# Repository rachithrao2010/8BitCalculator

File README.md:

Hey everyone!
This is my 8 bit calculator. it uses 8 1 bit full adders chained together. each 1 bit full adder module contains 9 NOR gates, with 2 2N3904 transistors, 2 10K resistors, and 1 1K resistor.
Heres a 3D render:

And here's a screensot of the routed board:

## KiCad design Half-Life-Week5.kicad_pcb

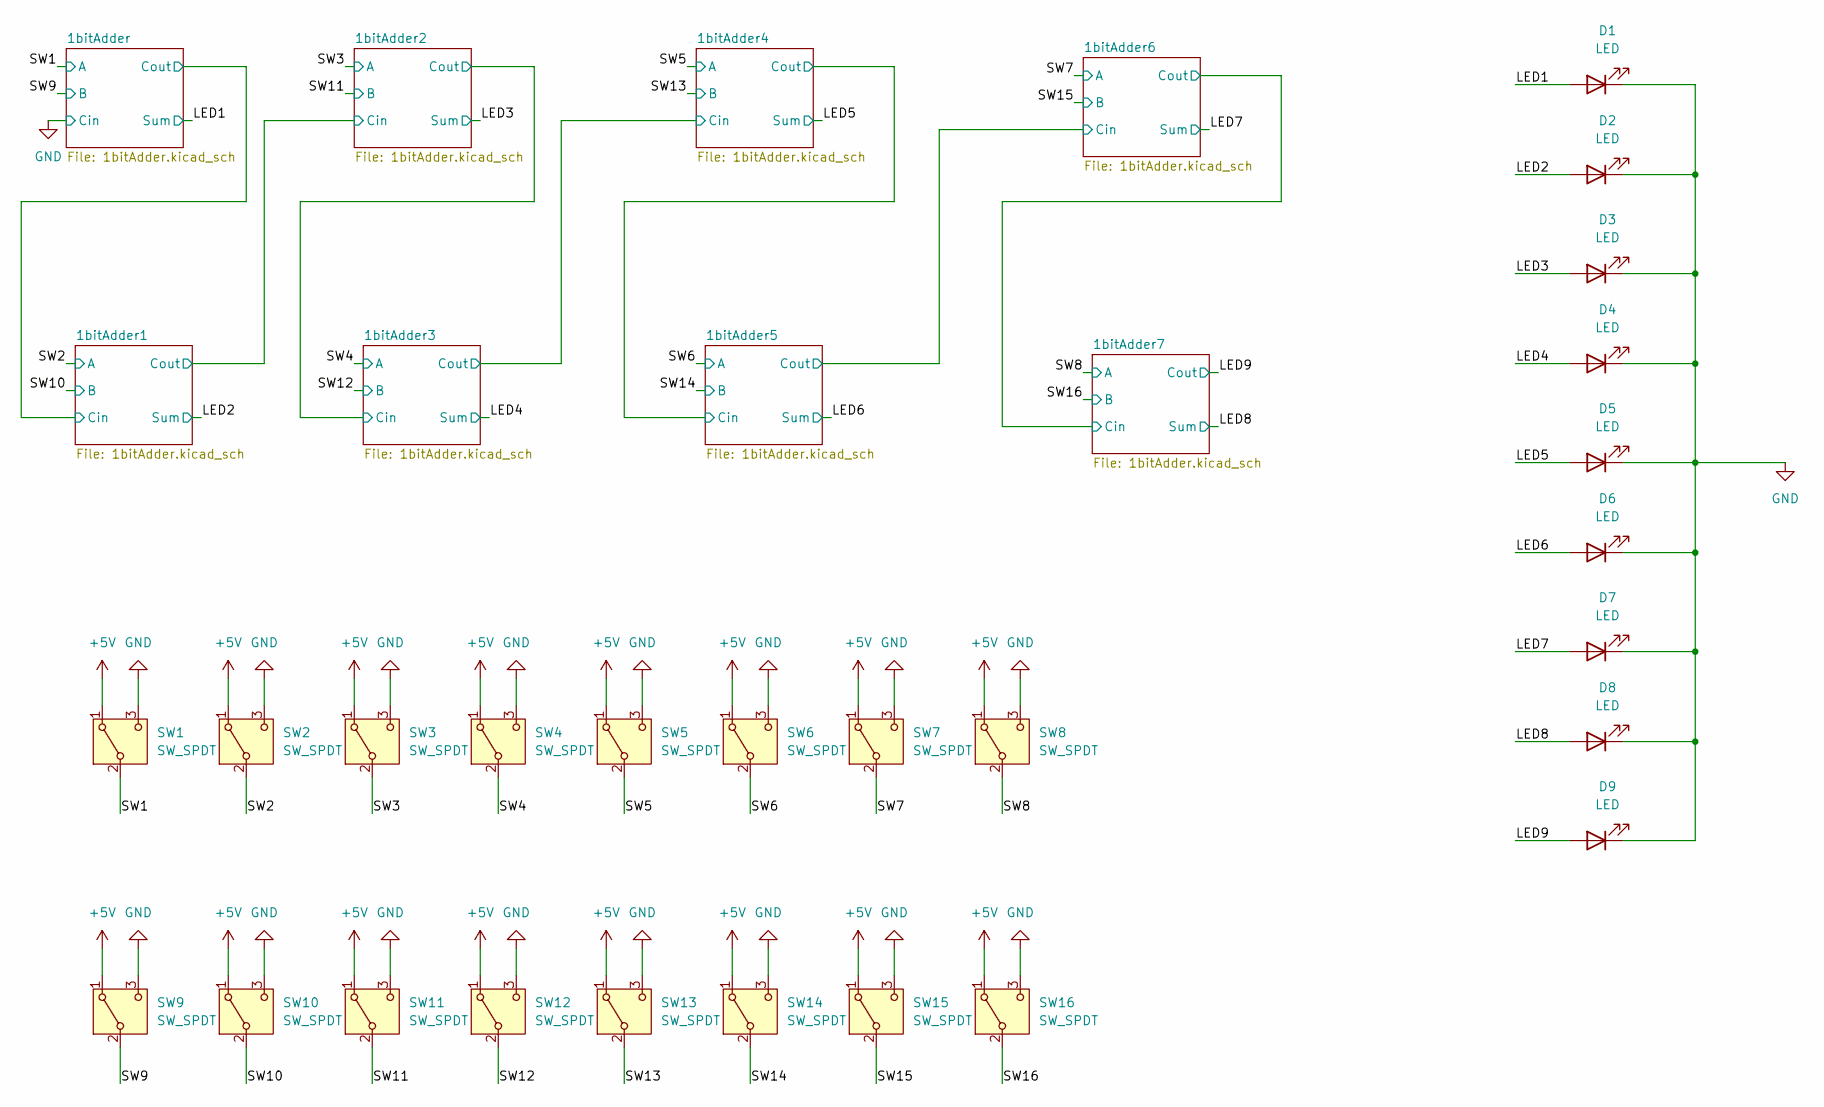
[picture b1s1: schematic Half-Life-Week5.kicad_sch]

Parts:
D1, D2, D3, D4, D5, D6, D7, D8, D9: LED; LED_D3.0mm
SW1, SW2, SW3, SW4, SW5, SW6, SW7, SW8, SW9, SW10, SW11, SW12, SW13, SW14, SW15, SW16: SW_SPDT; SW_Slide_SPDT_Straight_CK_OS102011MS2Q

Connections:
+5V: SW1.1 (A), SW2.1 (A), SW3.1 (A), SW4.1 (A), SW5.1 (A), SW6.1 (A), SW7.1 (A), SW8.1 (A), SW9.1 (A), SW10.1 (A), SW11.1 (A), SW12.1 (A), SW13.1 (A), SW14.1 (A), SW15.1 (A), SW16.1 (A); also elsewhere on the board
/LED1: D1.2 (A); also elsewhere on the board
/LED2: D2.2 (A); also elsewhere on the board
/LED3: D3.2 (A); also elsewhere on the board
/LED4: D4.2 (A); also elsewhere on the board
/LED5: D5.2 (A); also elsewhere on the board
/LED6: D6.2 (A); also elsewhere on the board
/LED7: D7.2 (A); also elsewhere on the board
/LED8: D8.2 (A); also elsewhere on the board
/LED9: D9.2 (A); also elsewhere on the board
/SW1: SW1.2 (B); also elsewhere on the board
/SW2: SW2.2 (B); also elsewhere on the board
/SW3: SW3.2 (B); also elsewhere on the board
/SW4: SW4.2 (B); also elsewhere on the board
/SW5: SW5.2 (B); also elsewhere on the board
/SW6: SW6.2 (B); also elsewhere on the board
/SW7: SW7.2 (B); also elsewhere on the board
/SW8: SW8.2 (B); also elsewhere on the board
/SW9: SW9.2 (B); also elsewhere on the board
/SW10: SW10.2 (B); also elsewhere on the board
/SW11: SW11.2 (B); also elsewhere on the board
/SW12: SW12.2 (B); also elsewhere on the board
/SW13: SW13.2 (B); also elsewhere on the board
/SW14: SW14.2 (B); also elsewhere on the board
/SW15: SW15.2 (B); also elsewhere on the board
/SW16: SW16.2 (B); also elsewhere on the board
GND: D1.1 (K), D2.1 (K), D3.1 (K), D4.1 (K), D5.1 (K), D6.1 (K), D7.1 (K), D8.1 (K), D9.1 (K), SW1.3 (C), SW2.3 (C), SW3.3 (C), SW4.3 (C), SW5.3 (C), SW6.3 (C), SW7.3 (C), SW8.3 (C), SW9.3 (C), SW10.3 (C), SW11.3 (C), SW12.3 (C), SW13.3 (C), SW14.3 (C), SW15.3 (C), SW16.3 (C); also elsewhere on the board

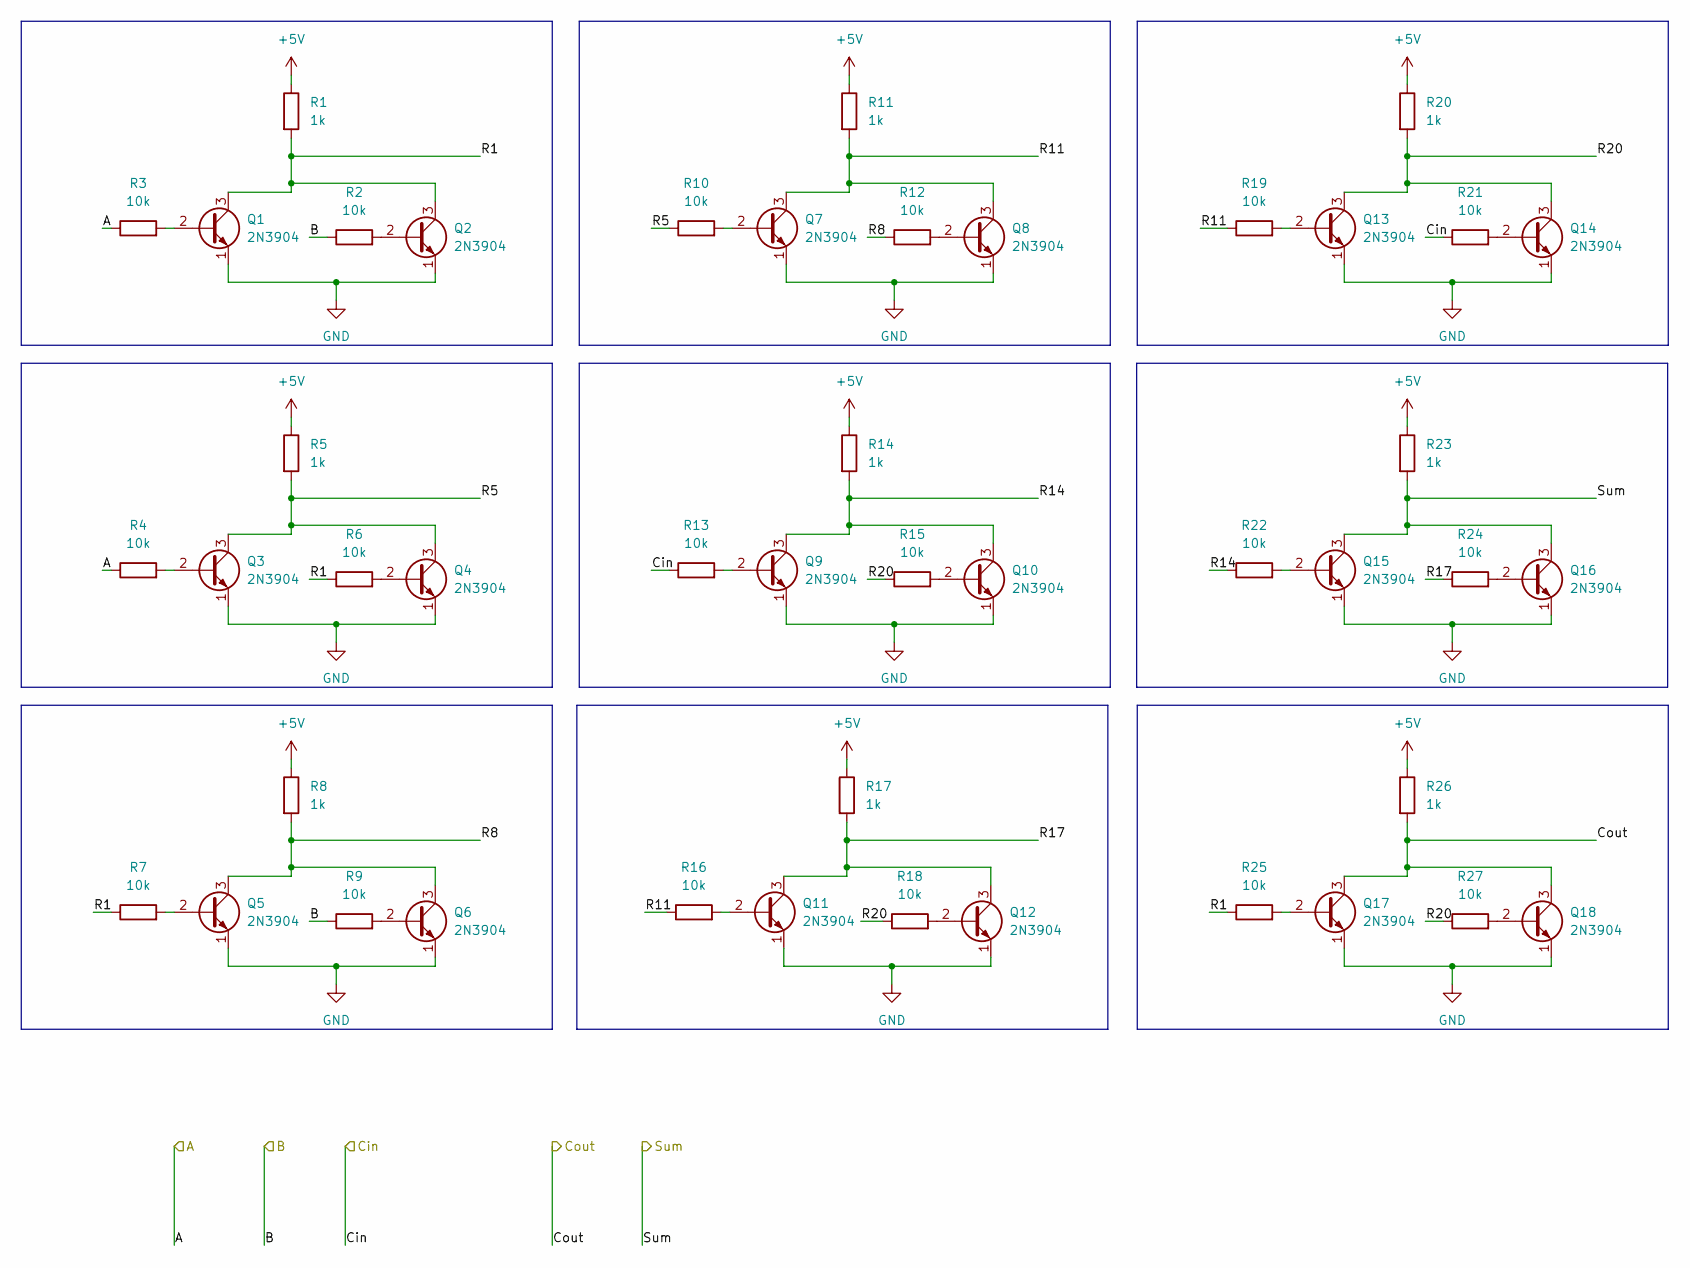
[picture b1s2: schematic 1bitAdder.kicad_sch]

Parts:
Q1, Q2, Q3, Q4, Q5, Q6, Q7, Q8, Q9, Q10, Q11, Q12, Q13, Q14, Q15, Q16, Q17, Q18: 2N3904; TO-92_Inline
R1, R5, R8, R11, R14, R17, R20, R23, R26: 1k; R_Axial_DIN0207_L6.3mm_D2.5mm_P7.62mm_Horizontal
R2, R3, R4, R6, R7, R9, R10, R12, R13, R15, R16, R18, R19, R21, R22, R24, R25, R27: 10k; R_Axial_DIN0207_L6.3mm_D2.5mm_P7.62mm_Horizontal

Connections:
+5V: R1.1, R5.1, R8.1, R11.1, R14.1, R17.1, R20.1, R23.1, R26.1; also elsewhere on the board
/1bitAdder/Cout: Q17.3 (C), Q18.3 (C), R26.2; also elsewhere on the board
/1bitAdder/R1: Q1.3 (C), Q2.3 (C), R1.2, R6.1, R7.1, R25.1
/1bitAdder/R5: Q3.3 (C), Q4.3 (C), R5.2, R10.1
/1bitAdder/R8: Q5.3 (C), Q6.3 (C), R8.2, R12.1
/1bitAdder/R11: Q7.3 (C), Q8.3 (C), R11.2, R16.1, R19.1
/1bitAdder/R14: Q9.3 (C), Q10.3 (C), R14.2, R22.1
/1bitAdder/R17: Q11.3 (C), Q12.3 (C), R17.2, R24.1
/1bitAdder/R20: Q13.3 (C), Q14.3 (C), R15.1, R18.1, R20.2, R27.1
/LED1: Q15.3 (C), Q16.3 (C), R23.2; also elsewhere on the board
/SW1: R3.1, R4.1; also elsewhere on the board
/SW9: R2.1, R9.1; also elsewhere on the board
GND: Q1.1 (E), Q2.1 (E), Q3.1 (E), Q4.1 (E), Q5.1 (E), Q6.1 (E), Q7.1 (E), Q8.1 (E), Q9.1 (E), Q10.1 (E), Q11.1 (E), Q12.1 (E), Q13.1 (E), Q14.1 (E), Q15.1 (E), Q16.1 (E), Q17.1 (E), Q18.1 (E), R13.1, R21.1; also elsewhere on the board
unnamed: Q1.2 (B), R3.2
unnamed: Q2.2 (B), R2.2
unnamed: Q3.2 (B), R4.2
unnamed: Q4.2 (B), R6.2
unnamed: Q5.2 (B), R7.2
unnamed: Q6.2 (B), R9.2
unnamed: Q7.2 (B), R10.2
unnamed: Q8.2 (B), R12.2
unnamed: Q9.2 (B), R13.2
unnamed: Q10.2 (B), R15.2
unnamed: Q11.2 (B), R16.2
unnamed: Q12.2 (B), R18.2
unnamed: Q13.2 (B), R19.2
unnamed: Q14.2 (B), R21.2
unnamed: Q15.2 (B), R22.2
unnamed: Q16.2 (B), R24.2
unnamed: Q17.2 (B), R25.2
unnamed: Q18.2 (B), R27.2

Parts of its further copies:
Q19, Q20, Q21, Q22, Q23, Q24, Q25, Q26, Q27, Q28, Q29, Q30, Q31, Q32, Q33, Q34, Q35, Q36, Q37, Q38, Q39, Q40, Q41, Q42, Q43, Q44, Q45, Q46, Q47, Q48, Q49, Q50, Q51, Q52, Q53, Q54, Q55, Q56, Q57, Q58, Q59, Q60, Q61, Q62, Q63, Q64, Q65, Q66, Q67, Q68, Q69, Q70, Q71, Q72, Q73, Q74, Q75, Q76, Q77, Q78, Q79, Q80, Q81, Q82, Q83, Q84, Q85, Q86, Q87, Q88, Q89, Q90, Q91, Q92, Q93, Q94, Q95, Q96, Q97, Q98, Q99, Q100, Q101, Q102, Q103, Q104, Q105, Q106, Q107, Q108, Q109, Q110, Q111, Q112, Q113, Q114, Q115, Q116, Q117, Q118, Q119, Q120, Q121, Q122, Q123, Q124, Q125, Q126, Q127, Q128, Q129, Q130, Q131, Q132, Q133, Q134, Q135, Q136, Q137, Q138, Q139, Q140, Q141, Q142, Q143, Q144: 2N3904; TO-92_Inline
R28, R29, R30, R34, R35, R36, R37, R38, R39, R43, R44, R45, R46, R47, R48, R52, R53, R54, R55, R56, R57, R61, R62, R63, R64, R65, R66, R70, R71, R72, R73, R74, R75, R79, R80, R81, R82, R83, R84, R88, R89, R90, R91, R92, R93, R97, R98, R99, R100, R101, R102, R106, R107, R108, R109, R110, R111, R115, R116, R117, R118, R119, R120, R124, R125, R126, R127, R128, R129, R133, R134, R135, R136, R137, R138, R142, R143, R144, R145, R146, R147, R151, R152, R153, R154, R155, R156, R160, R161, R162, R163, R164, R165, R169, R170, R171, R172, R173, R174, R178, R179, R180, R181, R182, R183, R187, R188, R189, R190, R191, R192, R196, R197, R198, R199, R200, R201, R205, R206, R207, R208, R209, R210, R214, R215, R216: 10k; R_Axial_DIN0207_L6.3mm_D2.5mm_P7.62mm_Horizontal
R31, R32, R33, R40, R41, R42, R49, R50, R51, R58, R59, R60, R67, R68, R69, R76, R77, R78, R85, R86, R87, R94, R95, R96, R103, R104, R105, R112, R113, R114, R121, R122, R123, R130, R131, R132, R139, R140, R141, R148, R149, R150, R157, R158, R159, R166, R167, R168, R175, R176, R177, R184, R185, R186, R193, R194, R195, R202, R203, R204, R211, R212, R213: 1k; R_Axial_DIN0207_L6.3mm_D2.5mm_P7.62mm_Horizontal

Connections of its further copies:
+5V: R31.1, R32.1, R33.1, R40.1, R41.1, R42.1, R49.1, R50.1, R51.1, R58.1, R59.1, R60.1, R67.1, R68.1, R69.1, R76.1, R77.1, R78.1, R85.1, R86.1, R87.1, R94.1, R95.1, R96.1, R103.1, R104.1, R105.1, R112.1, R113.1, R114.1, R121.1, R122.1, R123.1, R130.1, R131.1, R132.1, R139.1, R140.1, R141.1, R148.1, R149.1, R150.1, R157.1, R158.1, R159.1, R166.1, R167.1, R168.1, R175.1, R176.1, R177.1, R184.1, R185.1, R186.1, R193.1, R194.1, R195.1, R202.1, R203.1, R204.1, R211.1, R212.1, R213.1; also elsewhere on the board
/1bitAdder1/Cout: Q33.3 (C), Q36.3 (C), R51.2, R66.1, R80.1
/1bitAdder1/R1: Q19.3 (C), Q22.3 (C), R30.1, R31.2, R35.1, R48.1
/1bitAdder1/R5: Q20.3 (C), Q23.3 (C), R32.2, R38.1
/1bitAdder1/R8: Q21.3 (C), Q24.3 (C), R33.2, R44.1
/1bitAdder1/R11: Q26.3 (C), Q29.3 (C), R37.1, R41.2, R47.1
/1bitAdder1/R14: Q27.3 (C), Q30.3 (C), R42.2, R46.1
/1bitAdder1/R17: Q25.3 (C), Q28.3 (C), R40.2, R52.1
/1bitAdder1/R20: Q32.3 (C), Q35.3 (C), R43.1, R45.1, R50.2, R54.1
/1bitAdder2/Cout: Q51.3 (C), Q54.3 (C), R78.2, R93.1, R107.1
/1bitAdder2/R1: Q37.3 (C), Q40.3 (C), R57.1, R58.2, R62.1, R75.1
/1bitAdder2/R5: Q38.3 (C), Q41.3 (C), R59.2, R65.1
/1bitAdder2/R8: Q39.3 (C), Q42.3 (C), R60.2, R71.1
/1bitAdder2/R11: Q44.3 (C), Q47.3 (C), R64.1, R68.2, R74.1
/1bitAdder2/R14: Q45.3 (C), Q48.3 (C), R69.2, R73.1
/1bitAdder2/R17: Q43.3 (C), Q46.3 (C), R67.2, R79.1
/1bitAdder2/R20: Q50.3 (C), Q53.3 (C), R70.1, R72.1, R77.2, R81.1
/1bitAdder3/Cout: Q69.3 (C), Q72.3 (C), R105.2, R120.1, R134.1
/1bitAdder3/R1: Q55.3 (C), Q58.3 (C), R84.1, R85.2, R89.1, R102.1
/1bitAdder3/R5: Q56.3 (C), Q59.3 (C), R86.2, R92.1
/1bitAdder3/R8: Q57.3 (C), Q60.3 (C), R87.2, R98.1
/1bitAdder3/R11: Q62.3 (C), Q65.3 (C), R91.1, R95.2, R101.1
/1bitAdder3/R14: Q63.3 (C), Q66.3 (C), R96.2, R100.1
/1bitAdder3/R17: Q61.3 (C), Q64.3 (C), R94.2, R106.1
/1bitAdder3/R20: Q68.3 (C), Q71.3 (C), R97.1, R99.1, R104.2, R108.1
/1bitAdder4/Cout: Q87.3 (C), Q90.3 (C), R132.2, R147.1, R161.1
/1bitAdder4/R1: Q73.3 (C), Q76.3 (C), R111.1, R112.2, R116.1, R129.1
/1bitAdder4/R5: Q74.3 (C), Q77.3 (C), R113.2, R119.1
/1bitAdder4/R8: Q75.3 (C), Q78.3 (C), R114.2, R125.1
/1bitAdder4/R11: Q80.3 (C), Q83.3 (C), R118.1, R122.2, R128.1
/1bitAdder4/R14: Q81.3 (C), Q84.3 (C), R123.2, R127.1
/1bitAdder4/R17: Q79.3 (C), Q82.3 (C), R121.2, R133.1
/1bitAdder4/R20: Q86.3 (C), Q89.3 (C), R124.1, R126.1, R131.2, R135.1
/1bitAdder5/Cout: Q105.3 (C), Q108.3 (C), R159.2, R174.1, R188.1
/1bitAdder5/R1: Q91.3 (C), Q94.3 (C), R138.1, R139.2, R143.1, R156.1
/1bitAdder5/R5: Q92.3 (C), Q95.3 (C), R140.2, R146.1
/1bitAdder5/R8: Q93.3 (C), Q96.3 (C), R141.2, R152.1
/1bitAdder5/R11: Q98.3 (C), Q101.3 (C), R145.1, R149.2, R155.1
/1bitAdder5/R14: Q99.3 (C), Q102.3 (C), R150.2, R154.1
/1bitAdder5/R17: Q97.3 (C), Q100.3 (C), R148.2, R160.1
/1bitAdder5/R20: Q104.3 (C), Q107.3 (C), R151.1, R153.1, R158.2, R162.1
/1bitAdder6/Cout: Q123.3 (C), Q126.3 (C), R186.2, R201.1, R215.1
/1bitAdder6/R1: Q109.3 (C), Q112.3 (C), R165.1, R166.2, R170.1, R183.1
/1bitAdder6/R5: Q110.3 (C), Q113.3 (C), R167.2, R173.1
/1bitAdder6/R8: Q111.3 (C), Q114.3 (C), R168.2, R179.1
/1bitAdder6/R11: Q116.3 (C), Q119.3 (C), R172.1, R176.2, R182.1
/1bitAdder6/R14: Q117.3 (C), Q120.3 (C), R177.2, R181.1
/1bitAdder6/R17: Q115.3 (C), Q118.3 (C), R175.2, R187.1
/1bitAdder6/R20: Q122.3 (C), Q125.3 (C), R178.1, R180.1, R185.2, R189.1
/1bitAdder7/R1: Q127.3 (C), Q130.3 (C), R192.1, R193.2, R197.1, R210.1
/1bitAdder7/R5: Q128.3 (C), Q131.3 (C), R194.2, R200.1
/1bitAdder7/R8: Q129.3 (C), Q132.3 (C), R195.2, R206.1
/1bitAdder7/R11: Q134.3 (C), Q137.3 (C), R199.1, R203.2, R209.1
/1bitAdder7/R14: Q135.3 (C), Q138.3 (C), R204.2, R208.1
/1bitAdder7/R17: Q133.3 (C), Q136.3 (C), R202.2, R214.1
/1bitAdder7/R20: Q140.3 (C), Q143.3 (C), R205.1, R207.1, R212.2, R216.1
/1bitAdder/Cout: R39.1, R53.1; also elsewhere on the board
/LED2: Q31.3 (C), Q34.3 (C), R49.2; also elsewhere on the board
/LED3: Q49.3 (C), Q52.3 (C), R76.2; also elsewhere on the board
/LED4: Q67.3 (C), Q70.3 (C), R103.2; also elsewhere on the board
/LED5: Q85.3 (C), Q88.3 (C), R130.2; also elsewhere on the board
/LED6: Q103.3 (C), Q106.3 (C), R157.2; also elsewhere on the board
/LED7: Q121.3 (C), Q124.3 (C), R184.2; also elsewhere on the board
/LED8: Q139.3 (C), Q142.3 (C), R211.2; also elsewhere on the board
/LED9: Q141.3 (C), Q144.3 (C), R213.2; also elsewhere on the board
/SW2: R28.1, R29.1; also elsewhere on the board
/SW3: R55.1, R56.1; also elsewhere on the board
/SW4: R82.1, R83.1; also elsewhere on the board
/SW5: R109.1, R110.1; also elsewhere on the board
/SW6: R136.1, R137.1; also elsewhere on the board
/SW7: R163.1, R164.1; also elsewhere on the board
/SW8: R190.1, R191.1; also elsewhere on the board
/SW10: R34.1, R36.1; also elsewhere on the board
/SW11: R61.1, R63.1; also elsewhere on the board
/SW12: R88.1, R90.1; also elsewhere on the board
/SW13: R115.1, R117.1; also elsewhere on the board
/SW14: R142.1, R144.1; also elsewhere on the board
/SW15: R169.1, R171.1; also elsewhere on the board
/SW16: R196.1, R198.1; also elsewhere on the board
GND: Q19.1 (E), Q20.1 (E), Q21.1 (E), Q22.1 (E), Q23.1 (E), Q24.1 (E), Q25.1 (E), Q26.1 (E), Q27.1 (E), Q28.1 (E), Q29.1 (E), Q30.1 (E), Q31.1 (E), Q32.1 (E), Q33.1 (E), Q34.1 (E), Q35.1 (E), Q36.1 (E), Q37.1 (E), Q38.1 (E), Q39.1 (E), Q40.1 (E), Q41.1 (E), Q42.1 (E), Q43.1 (E), Q44.1 (E), Q45.1 (E), Q46.1 (E), Q47.1 (E), Q48.1 (E), Q49.1 (E), Q50.1 (E), Q51.1 (E), Q52.1 (E), Q53.1 (E), Q54.1 (E), Q55.1 (E), Q56.1 (E), Q57.1 (E), Q58.1 (E), Q59.1 (E), Q60.1 (E), Q61.1 (E), Q62.1 (E), Q63.1 (E), Q64.1 (E), Q65.1 (E), Q66.1 (E), Q67.1 (E), Q68.1 (E), Q69.1 (E), Q70.1 (E), Q71.1 (E), Q72.1 (E), Q73.1 (E), Q74.1 (E), Q75.1 (E), Q76.1 (E), Q77.1 (E), Q78.1 (E), Q79.1 (E), Q80.1 (E), Q81.1 (E), Q82.1 (E), Q83.1 (E), Q84.1 (E), Q85.1 (E), Q86.1 (E), Q87.1 (E), Q88.1 (E), Q89.1 (E), Q90.1 (E), Q91.1 (E), Q92.1 (E), Q93.1 (E), Q94.1 (E), Q95.1 (E), Q96.1 (E), Q97.1 (E), Q98.1 (E), Q99.1 (E), Q100.1 (E), Q101.1 (E), Q102.1 (E), Q103.1 (E), Q104.1 (E), Q105.1 (E), Q106.1 (E), Q107.1 (E), Q108.1 (E), Q109.1 (E), Q110.1 (E), Q111.1 (E), Q112.1 (E), Q113.1 (E), Q114.1 (E), Q115.1 (E), Q116.1 (E), Q117.1 (E), Q118.1 (E), Q119.1 (E), Q120.1 (E), Q121.1 (E), Q122.1 (E), Q123.1 (E), Q124.1 (E), Q125.1 (E), Q126.1 (E), Q127.1 (E), Q128.1 (E), Q129.1 (E), Q130.1 (E), Q131.1 (E), Q132.1 (E), Q133.1 (E), Q134.1 (E), Q135.1 (E), Q136.1 (E), Q137.1 (E), Q138.1 (E), Q139.1 (E), Q140.1 (E), Q141.1 (E), Q142.1 (E), Q143.1 (E), Q144.1 (E); also elsewhere on the board
unnamed: Q19.2 (B), R28.2
unnamed: Q20.2 (B), R29.2
unnamed: Q21.2 (B), R30.2
unnamed: Q22.2 (B), R34.2
unnamed: Q23.2 (B), R35.2
unnamed: Q24.2 (B), R36.2
unnamed: Q25.2 (B), R37.2
unnamed: Q26.2 (B), R38.2
unnamed: Q27.2 (B), R39.2
unnamed: Q28.2 (B), R43.2
unnamed: Q29.2 (B), R44.2
unnamed: Q30.2 (B), R45.2
unnamed: Q31.2 (B), R46.2
unnamed: Q32.2 (B), R47.2
unnamed: Q33.2 (B), R48.2
unnamed: Q34.2 (B), R52.2
unnamed: Q35.2 (B), R53.2
unnamed: Q36.2 (B), R54.2
unnamed: Q37.2 (B), R55.2
unnamed: Q38.2 (B), R56.2
unnamed: Q39.2 (B), R57.2
unnamed: Q40.2 (B), R61.2
unnamed: Q41.2 (B), R62.2
unnamed: Q42.2 (B), R63.2
unnamed: Q43.2 (B), R64.2
unnamed: Q44.2 (B), R65.2
unnamed: Q45.2 (B), R66.2
unnamed: Q46.2 (B), R70.2
unnamed: Q47.2 (B), R71.2
unnamed: Q48.2 (B), R72.2
unnamed: Q49.2 (B), R73.2
unnamed: Q50.2 (B), R74.2
unnamed: Q51.2 (B), R75.2
unnamed: Q52.2 (B), R79.2
unnamed: Q53.2 (B), R80.2
unnamed: Q54.2 (B), R81.2
unnamed: Q55.2 (B), R82.2
unnamed: Q56.2 (B), R83.2
unnamed: Q57.2 (B), R84.2
unnamed: Q58.2 (B), R88.2
unnamed: Q59.2 (B), R89.2
unnamed: Q60.2 (B), R90.2
unnamed: Q61.2 (B), R91.2
unnamed: Q62.2 (B), R92.2
unnamed: Q63.2 (B), R93.2
unnamed: Q64.2 (B), R97.2
unnamed: Q65.2 (B), R98.2
unnamed: Q66.2 (B), R99.2
unnamed: Q67.2 (B), R100.2
unnamed: Q68.2 (B), R101.2
unnamed: Q69.2 (B), R102.2
unnamed: Q70.2 (B), R106.2
unnamed: Q71.2 (B), R107.2
unnamed: Q72.2 (B), R108.2
unnamed: Q73.2 (B), R109.2
unnamed: Q74.2 (B), R110.2
unnamed: Q75.2 (B), R111.2
unnamed: Q76.2 (B), R115.2
unnamed: Q77.2 (B), R116.2
unnamed: Q78.2 (B), R117.2
unnamed: Q79.2 (B), R118.2
unnamed: Q80.2 (B), R119.2
unnamed: Q81.2 (B), R120.2
unnamed: Q82.2 (B), R124.2
unnamed: Q83.2 (B), R125.2
unnamed: Q84.2 (B), R126.2
unnamed: Q85.2 (B), R127.2
unnamed: Q86.2 (B), R128.2
unnamed: Q87.2 (B), R129.2
unnamed: Q88.2 (B), R133.2
unnamed: Q89.2 (B), R134.2
unnamed: Q90.2 (B), R135.2
unnamed: Q91.2 (B), R136.2
unnamed: Q92.2 (B), R137.2
unnamed: Q93.2 (B), R138.2
unnamed: Q94.2 (B), R142.2
unnamed: Q95.2 (B), R143.2
unnamed: Q96.2 (B), R144.2
unnamed: Q97.2 (B), R145.2
unnamed: Q98.2 (B), R146.2
unnamed: Q99.2 (B), R147.2
unnamed: Q100.2 (B), R151.2
unnamed: Q101.2 (B), R152.2
unnamed: Q102.2 (B), R153.2
unnamed: Q103.2 (B), R154.2
unnamed: Q104.2 (B), R155.2
unnamed: Q105.2 (B), R156.2
unnamed: Q106.2 (B), R160.2
unnamed: Q107.2 (B), R161.2
unnamed: Q108.2 (B), R162.2
unnamed: Q109.2 (B), R163.2
unnamed: Q110.2 (B), R164.2
unnamed: Q111.2 (B), R165.2
unnamed: Q112.2 (B), R169.2
unnamed: Q113.2 (B), R170.2
unnamed: Q114.2 (B), R171.2
unnamed: Q115.2 (B), R172.2
unnamed: Q116.2 (B), R173.2
unnamed: Q117.2 (B), R174.2
unnamed: Q118.2 (B), R178.2
unnamed: Q119.2 (B), R179.2
unnamed: Q120.2 (B), R180.2
unnamed: Q121.2 (B), R181.2
unnamed: Q122.2 (B), R182.2
unnamed: Q123.2 (B), R183.2
unnamed: Q124.2 (B), R187.2
unnamed: Q125.2 (B), R188.2
unnamed: Q126.2 (B), R189.2
unnamed: Q127.2 (B), R190.2
unnamed: Q128.2 (B), R191.2
unnamed: Q129.2 (B), R192.2
unnamed: Q130.2 (B), R196.2
unnamed: Q131.2 (B), R197.2
unnamed: Q132.2 (B), R198.2
unnamed: Q133.2 (B), R199.2
unnamed: Q134.2 (B), R200.2
unnamed: Q135.2 (B), R201.2
unnamed: Q136.2 (B), R205.2
unnamed: Q137.2 (B), R206.2
unnamed: Q138.2 (B), R207.2
unnamed: Q139.2 (B), R208.2
unnamed: Q140.2 (B), R209.2
unnamed: Q141.2 (B), R210.2
unnamed: Q142.2 (B), R214.2
unnamed: Q143.2 (B), R215.2
unnamed: Q144.2 (B), R216.2

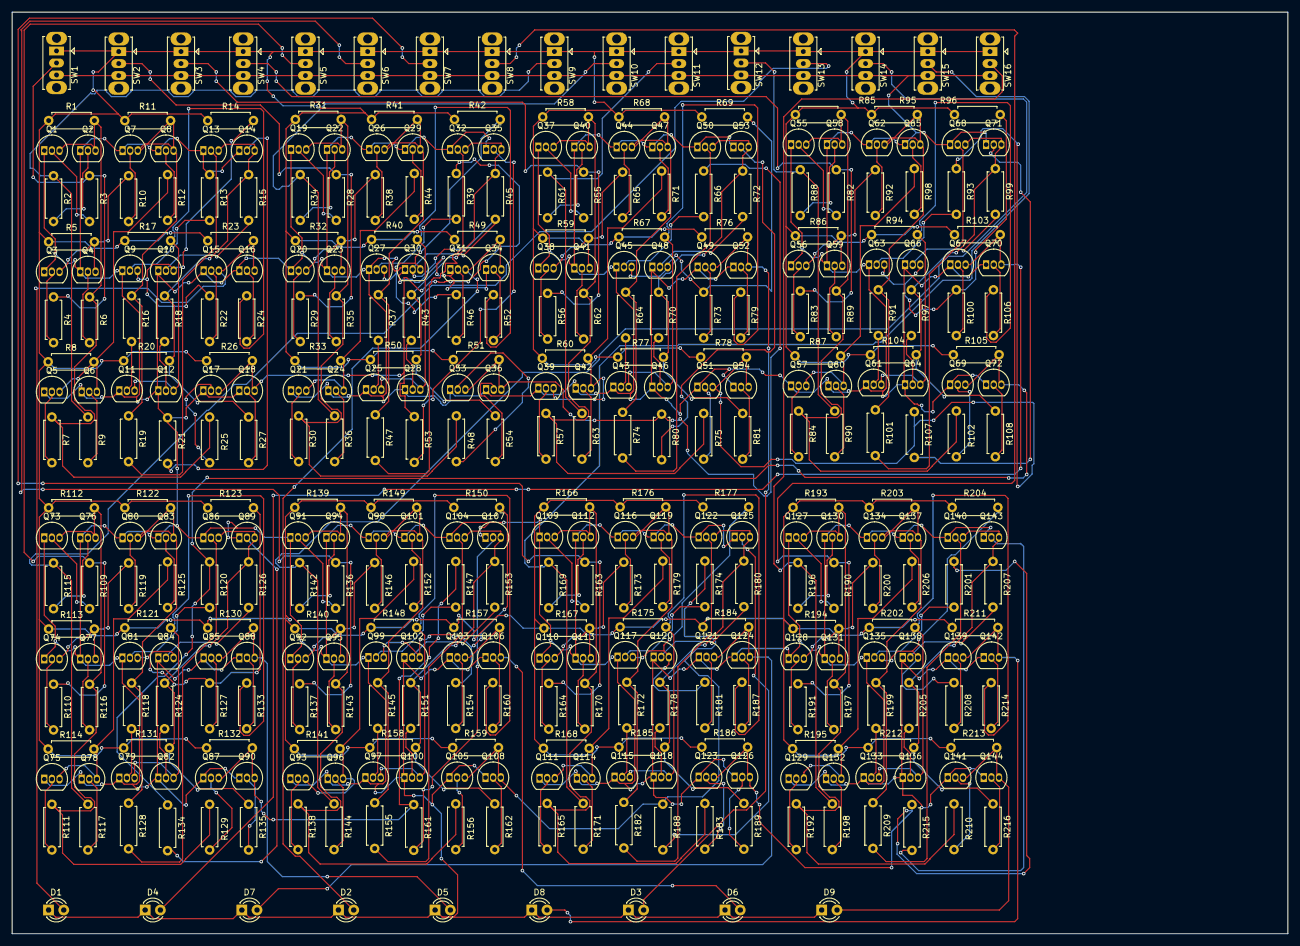
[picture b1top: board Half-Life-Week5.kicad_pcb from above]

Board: 2 copper layers, 212.5 x 153.5 mm, 385 parts (0 on the bottom side), 234 nets.
